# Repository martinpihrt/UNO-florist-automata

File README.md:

UNO florist automata Readme  
====

## UNO florist automata - Zavlažovač květin je založený na platformě Arduino a desce Arduino UNO<br>
(procesor ATMEGA328 a vlastní deska spojů)

Celý projekt je založen jako volný zdroj (lze použít pro nekomerční použití a přizpůsobit si k obrazu svému).<br>
K řídící desce je připojeno teplotní čidlo DS18B20, které měří teplotu půdy (pro možnost regulace zavlažování dle teploty)<br>
K řídící desce je také připojeno čidlo vlhkosti s frekvenčním výstupem 50Hz-5kHz (pro možnost regulace zavlažování dle vlhkosti) https://pihrt.com/elektronika/272-snimac-vlhkosti-pro-zalevaci-automat<br>
Veškeré nastavení automatu se provádí pomocí tlačítek a zobrazení údajů na 16x2 LCD displeji.<br>
Automat byl vyvinutý pro vertikální zavlažování rostlin, které má svá specifika zavlažování.<br>

## Pro více informací navštivte web...
Martin Pihrt - www.pihrt.com: https://pihrt.com/elektronika/400-uno-florist-automata<br>

## Pohled na desku a připojení čidel

## Video (fw 1.00 beta)

## Nastavení zavlažování dle dnů od pondělí do neděle

## Nastavení 3 nezávislých časů pro zavlažování s různou dobou provozu čerpadla

## Regulace dle vlhkosti
a) pokud je daný den a je čas programu 1 nebo je čas programu 2 nebo je čas programu 3 a vlhkost < 40% bude výsledná doba trvání závlahy + 1/2 trvání závlahy nastavené doby v menu. Tj. 150% času.<br>
b) pokud je daný den a je čas programu 1 nebo je čas programu 2 nebo je čas programu 3 a vlhkost >= 40% a < 60% bude výsledná doba trvání závlahy stejná jako nastavená doba v menu. Tj. 100% času.<br>
c) pokud je daný den a je čas programu 1 nebo je čas programu 2 a vlhkost >= 60% a < 80% bude výsledná doba trvání závlahy stejná jako nastavená doba v menu. Tj. 100% času.<br>
d) pokud je daný den a je čas programu 1 a vlhkost >= 60% bude výsledná doba trvání závlahy stejná jako nastavená doba v menu. Tj. 100% času.<br>
Z výše uvedeného vyplývá, že některé programy se s ohledem na vlhkost v určitém rozsahu vůbec nespustí, nebo bude výsledný čas upraven.<br>

<b>V žádném případě nepoužívejte obě regulace současně!</b>

## Regulece dle teploty
a) pokud je daný den a je čas programu 1 nebo je čas programu 2 nebo je čas programu 3 a teplota > 40°C bude výsledná doba trvání závlahy + 1/2 trvání závlahy nastavené doby v menu. Tj. 150% času.<br>
b) pokud je daný den a je čas programu 1 nebo je čas programu 2 nebo je čas programu 3 a teplota >= 30°C a < 40°C bude výsledná doba trvání závlahy stejná jako nastavená doba v menu. Tj. 100% času.<br>
c) pokud je daný den a je čas programu 1 nebo je čas programu 2 a teplota >= 20°C a < 30°C bude výsledná doba trvání závlahy stejná jako nastavená doba v menu. Tj. 100% času.<br>
d) pokud je daný den a je čas programu 1 a teplota >= 5°C a < 20°C bude výsledná doba trvání závlahy stejná jako nastavená doba v menu. Tj. 100% času.<br>
Z výše uvedeného vyplývá, že některé programy se s ohledem na teplotu v určitém rozsahu vůbec nespustí, nebo bude výsledný čas upraven.<br>

<b>V žádném případě nepoužívejte obě regulace současně!</b>

## Cyklování výstupu
V menu lze nastavit po jaké době běhu programu (1, 2, 3) se má výstup čerpadla vypnout a jako dobu má čekat vypnutý. Tato funkce umožňuje cyklování výstupu pro lepší vsakování vody do půdy (nedojde k přetékání květináče, ale k postupnému vsaku vody)<br>

Pokud nepožadujeme funkci cyklování nastavíme v menu "vypnout na dobu" na hodnotu 0s" a "vypnout čerpadlo po" na maximální hodnotu 250s.<br>
V grafu je vidět spínání výstupu (zap/vyp cyklování) s ohledem na vlhkost.<br>

## Nastavení datumu a času
Zleva nastavujeme den, měsíc, rok, hodina a minuta. Vteřina se při uložení nastaví na "0". Čas je ukládán do obvodu RTC DS1307.<br>

## Smazání do továrního nastavení
Pokud chceme zařízení vymazat do továrního nastavení stiskneme v menu jako níže na obrázku "ANO".<br>
<br>
* Výchozí údaje po resetu:<br>
* program 1 čas pro zavlažování 6:00<br>
* doba 30s<br>
* program 2 čas pro zavlažování 18:00<br>
* doba 30s<br>
* program 3 čas pro zavlažování 9:00<br> 
* doba 30s<br>
* vypnout čerpadlo po 5s<br>
* vypnout na dobu 20s<br>
* nepoužívat regulaci teplotou<br>
* nepoužívat regulaci vhlkostí<br>
* zavlažovat ve dnech po-ne<br>

## Uložit nastavení
Všechny parametry se ukládají do trvalé paměti EEPROM.<br>

## Připojení vstupů a výstupů  
* LCD:                    pin 8, 9,  2,  3,  6,  7 (Rs, E,DB4,DB5,DB6,DB7)<br>
* LCD podsvícení:         pin 10<br>
* Tlačítka IN:            pin 14 (A0 dělič 5 tlačítek)<br>
* Čidlo vlhka IN:         pin 5 (měří se frekvence ze snímače vlhkosti)<br>
* Serial:                 pin 0, 1<br>
* I2C:                    pin 18 (A4 SDA), 19 (A5 SCL) používá DS1307 adr. 0x68<br>
* Teplota:                pin 16  DS18B20 rudá +5V, černá GND, modrá (bílá) Data<br>
* Čerpadlo:               pin 17 (pro výstup - čerpadlo)<br>

## Verze FW, HW
* 1.00 výchozí verze desky a programu (měření vlhkosti pomocí frekvence)
* 1.10 upravená verze HW (přidán konektor na vstup A1) a FW (možnost měření vlhkosti pomocí sondy s napěťovým výstupem) příklad použité sondy: https://www.diymore.cc/products/2pcs-capacitive-soil-moisture-sensor-v1-2-analog-corrosion-resistant-dc-3-3-5-5v)
* 1.11 příprava na podporu více jazyků (zatím není hotové)

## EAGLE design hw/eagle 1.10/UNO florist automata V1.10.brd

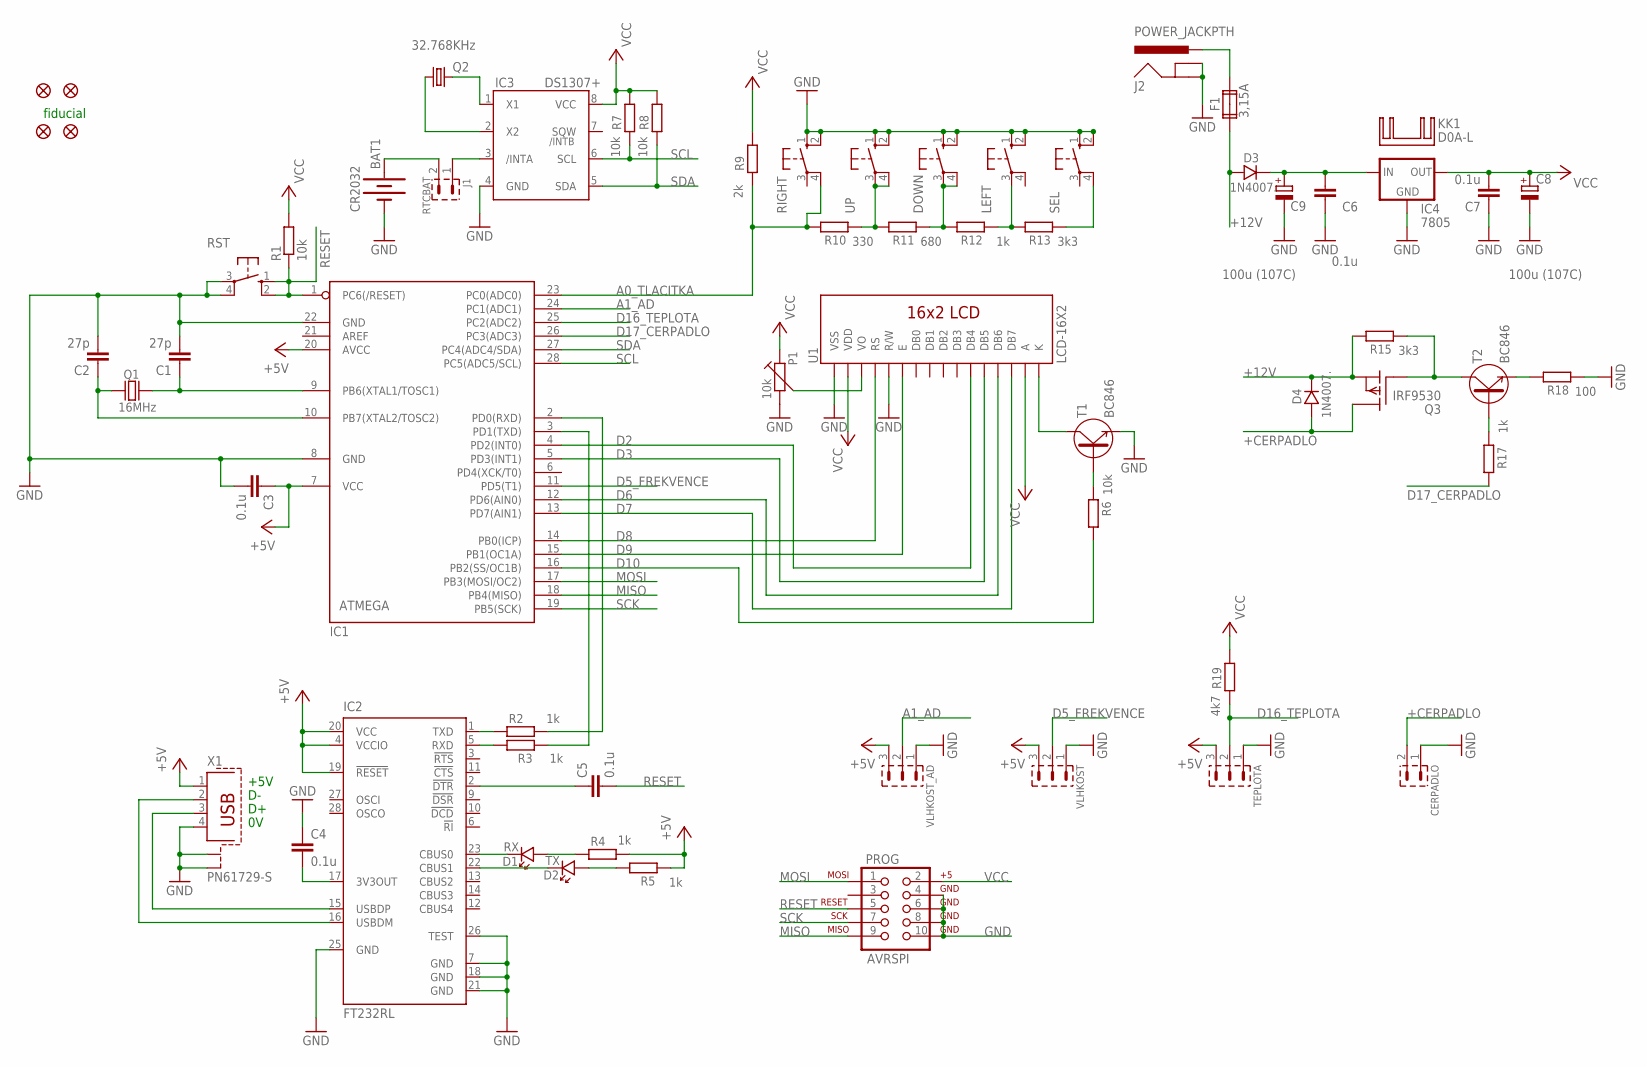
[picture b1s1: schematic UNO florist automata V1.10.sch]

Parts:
BAT1: CR2032; BATTCOM_20MM_PTH
C1, C2: 27p; C1206
C3, C4, C5, C6, C7: 0.1u; C1206
C8, C9: 100u (107C); C/6032-28W
CERPADLO: PSH02-02P
D1: RX; P1206
D2: TX; P1206
D3, D4: 1N4007.; SM-1
DOWN: 10-XX; B3F-10XX
F1: 3,15A; FUSE1
FID1, FID2, FID3, FID4: FIDUCIAL1.5X3; FIDUCIAL-1.5X3
IC1: ATMEGA; DIL28-3
IC2: FT232RL; SSOP28
IC3: DS1307+; SO08
IC4: 7805; 78XXL
J1: RTCBAT; S1G2_JUM
J2: POWER_JACKPTH; POWER_JACK_PTH
KK1: D0A-L; D02A-L
LEFT: 10-XX; B3F-10XX
P1: 10k; PT10V
PROG: AVRSPI; 2X5-SHROUDED_LOCK
Q1: 16MHz; HC-49U
Q2: 32.768KHz; TC38H
Q3: IRF9530; TO220
R1, R6, R7, R8: 10k; M1206
R2, R3, R4, R5, R12, R17: 1k; M1206
R9: 2k; M1206
R10: 330; M1206
R11: 680; M1206
R13, R15: 3k3; M1206
R18: 100; M1206
R19: 4k7; M1206
RIGHT: 10-XX; B3F-10XX
RST: 10-XX; B3F-10XX
SEL: 10-XX; B3F-10XX
T1, T2: BC846; SOT-23
TEPLOTA: PSH02-03P
U1: LCD-16X2; LCD-16X2_NOSILK
UP: 10-XX; B3F-10XX
VLHKOST: PSH02-03P
VLHKOST_AD: PSH02-03P
X1: PN61729-S

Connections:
+12V: D3.A, D4.K, F1.1A, Q3.3 (S), R15.2
+CERPADLO: CERPADLO.2, D4.A, Q3.2 (D)
A: IC3.2 (X2), Q2.1
A0_TLACITKA: IC1.23 (PC0(ADC0)), R9.1, R10.2, RIGHT.4 (P1)
A1_AD: IC1.24 (PC1(ADC1)), VLHKOST_AD.2
D2: IC1.4 (PD2(INT0)), U1.11 (DB4)
D3: IC1.5 (PD3(INT1)), U1.12 (DB5)
D5_FREKVENCE: IC1.11 (PD5(T1)), VLHKOST.2
D6: IC1.12 (PD6(AIN0)), U1.13 (DB6)
D7: IC1.13 (PD7(AIN1)), U1.14 (DB7)
D8: IC1.14 (PB0(ICP)), U1.4 (RS)
D9: IC1.15 (PB1(OC1A)), U1.6 (E)
D10: IC1.16 (PB2(SS/OC1B)), R6.2
D16_TEPLOTA: IC1.25 (PC2(ADC2)), R19.1, TEPLOTA.2
D17_CERPADLO: IC1.26 (PC3(ADC3)), R17.2
GND: BAT1.2 (-), C1.2, C2.2, C3.2, C4.1, C6.1, C7.1, C8.-, C9.-, CERPADLO.1, DOWN.1 (S), DOWN.2 (S1), IC1.8 (GND), IC1.22 (GND), IC2.7 (GND), IC2.18 (GND), IC2.21 (GND), IC2.25 (GND), IC2.26 (TEST), IC3.4 (GND), IC4.GND, J2.GND, J2.GNDBREAK, LEFT.1 (S), LEFT.2 (S1), P1.2, PROG.4, PROG.6, PROG.8, PROG.10, R18.1, RIGHT.1 (S), RIGHT.2 (S1), RST.3, RST.4 (P1), SEL.1 (S), SEL.2 (S1), T1.2 (E), TEPLOTA.1, U1.1 (VSS), U1.5 (R/W), UP.1 (S), UP.2 (S1), VLHKOST.1, VLHKOST_AD.1, X1.4, X1.S1, X1.S2
MISO: IC1.18 (PB4(MISO)), PROG.9
MOSI: IC1.17 (PB3(MOSI/OC2)), PROG.1
unnamed: IC2.16 (USBDM), X1.2
unnamed: IC2.15 (USBDP), X1.3
unnamed: C4.2, IC2.17 (3V3OUT)
unnamed: IC2.1 (TXD), R2.1
unnamed: IC2.5 (RXD), R3.2
unnamed: IC1.2 (PD0(RXD)), R2.2
unnamed: IC1.3 (PD1(TXD)), R3.1
unnamed: C5.1, IC2.2 (!DTR)
unnamed: D1.K, IC2.23 (CBUS0)
unnamed: D1.A, R4.1
unnamed: D2.K, IC2.22 (CBUS1)
unnamed: D2.A, R5.2
unnamed: BAT1.1 (+), J1.2
unnamed: IC3.3 (/INTA), J1.1
unnamed: T1.3 (C), U1.16 (K)
unnamed: R10.1, R11.2, UP.3, UP.4 (P1)
unnamed: DOWN.3, DOWN.4 (P1), R11.1, R12.2
unnamed: LEFT.3, R12.1, R13.2
unnamed: R13.1, SEL.4 (P1)
unnamed: F1.2A, J2.PWR
unnamed: C1.1, IC1.9 (PB6(XTAL1/TOSC1)), Q1.2
unnamed: C6.2, C9.+, D3.K, IC4.IN
unnamed: R6.1, T1.1 (B)
unnamed: C2.1, IC1.10 (PB7(XTAL2/TOSC2)), Q1.1
unnamed: Q3.1 (G), R15.1, T2.3 (C)
unnamed: R18.2, T2.2 (E)
unnamed: R17.1, T2.1 (B)
unnamed: P1.3, U1.3 (VO)
Q1: IC3.1 (X1), Q2.2
RESET: C5.2, IC1.1 (PC6(/RESET)), PROG.5, R1.1, RST.1 (S), RST.2 (S1)
SCK: IC1.19 (PB5(SCK)), PROG.7
SCL: IC1.28 (PC5(ADC5/SCL)), IC3.6 (SCL), R7.1
SDA: IC1.27 (PC4(ADC4/SDA)), IC3.5 (SDA), R8.1
VCC: C3.1, C7.2, C8.+, IC1.7 (VCC), IC1.20 (AVCC), IC2.4 (VCCIO), IC2.19 (!RESET), IC2.20 (VCC), IC3.8 (VCC), IC4.OUT, P1.1, PROG.2, R1.2, R4.2, R5.1, R7.2, R8.2, R9.2, R19.2, TEPLOTA.3, U1.2 (VDD), U1.15 (A), VLHKOST.3, VLHKOST_AD.3, X1.1

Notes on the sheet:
+5V
fiducial

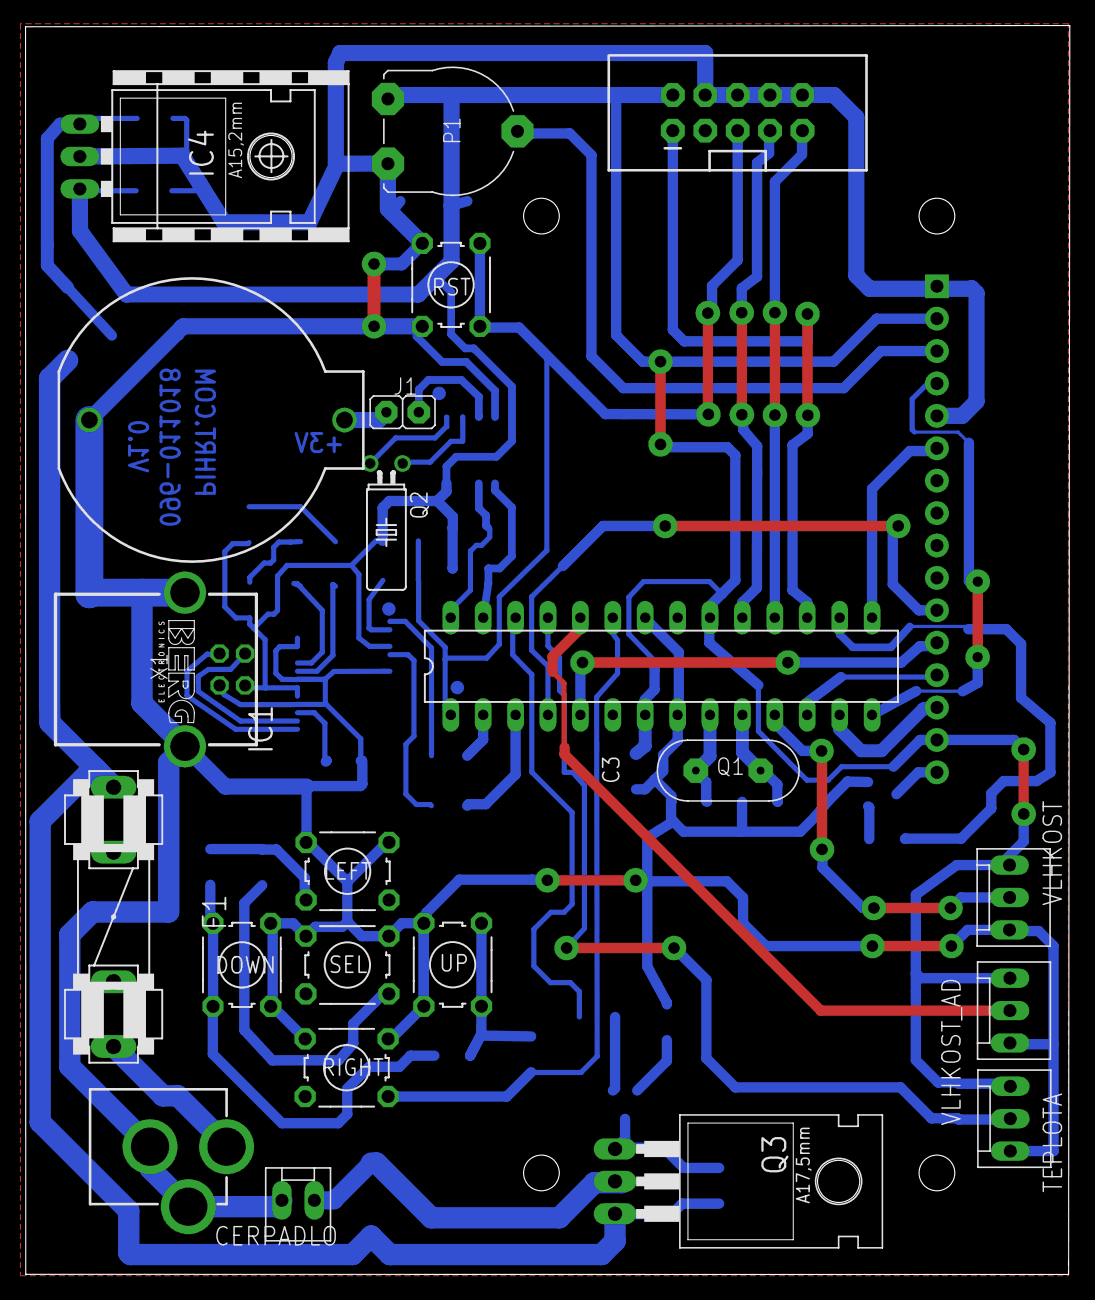
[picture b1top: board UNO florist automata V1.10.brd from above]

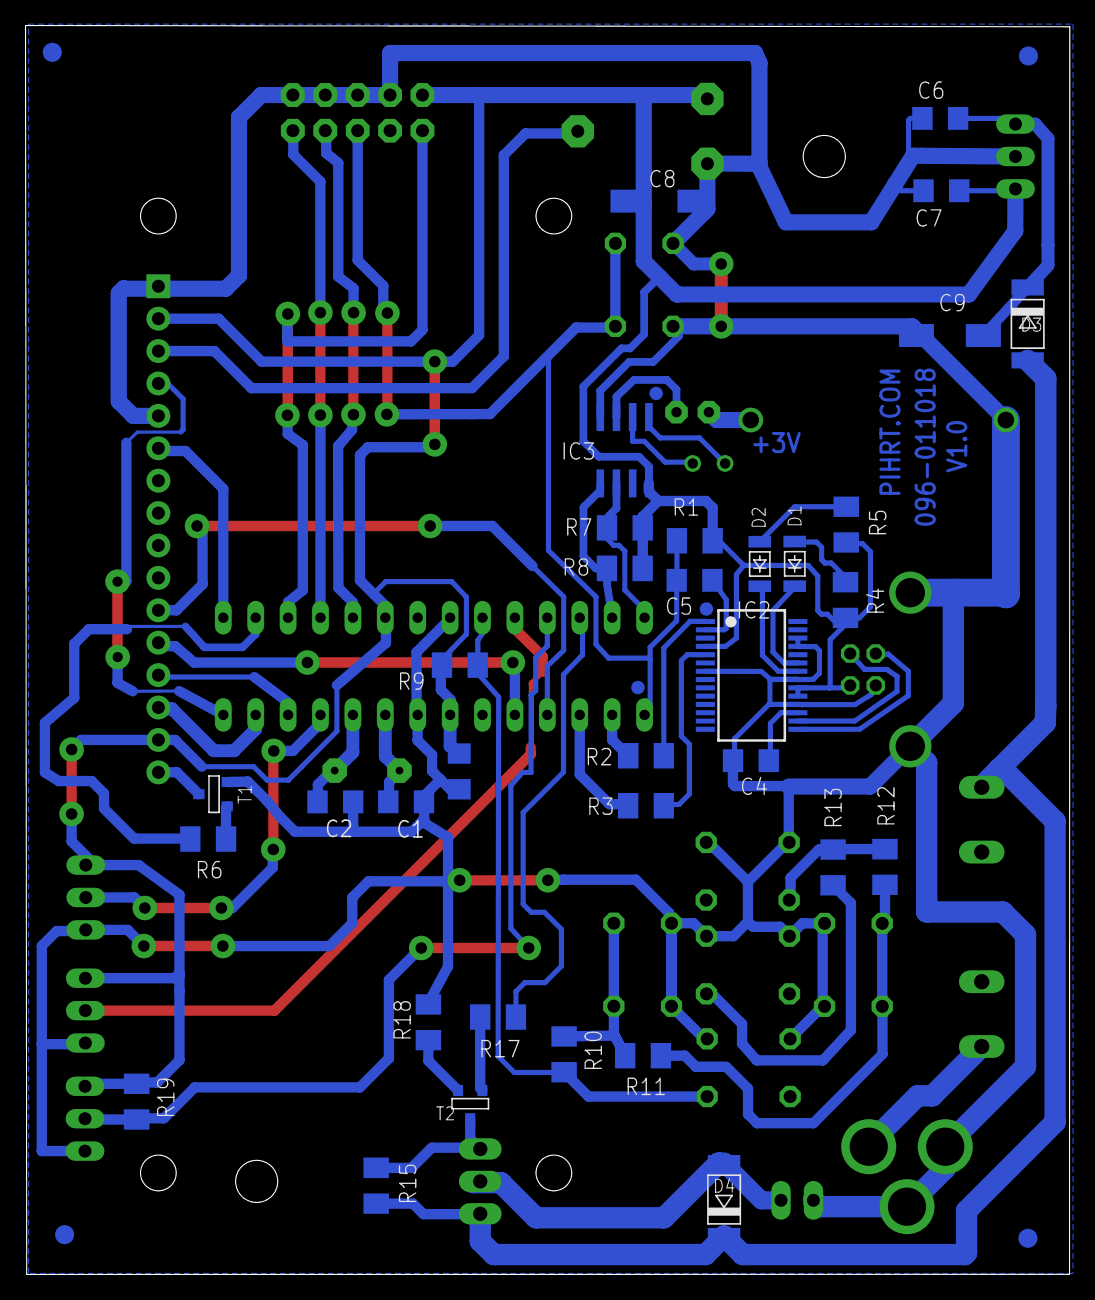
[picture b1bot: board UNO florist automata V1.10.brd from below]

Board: 2 copper layers, 81.9 x 97.9 mm, 62 parts (38 on the bottom side), 52 nets.

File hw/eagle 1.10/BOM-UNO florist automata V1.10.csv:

"Part";"Value";"Device";"Package";"Description";"MF";"MPN";"OC_FARNELL";"OC_NEWARK";"PROD_ID";
"BAT1";"CR2032";"BATTERY20PTH";"BATTCOM_20MM_PTH";"Battery Holders";"";"";"";"";"";
"C1";"27p";"C-EUC1206";"C1206";"CAPACITOR, European symbol";"";"";"";"";"";
"C2";"27p";"C-EUC1206";"C1206";"CAPACITOR, European symbol";"";"";"";"";"";
"C3";"0.1u";"C-EUC1206";"C1206";"CAPACITOR, European symbol";"";"";"";"";"";
"C4";"0.1u";"C-EUC1206";"C1206";"CAPACITOR, European symbol";"";"";"";"";"";
"C5";"0.1u";"C-EUC1206";"C1206";"CAPACITOR, European symbol";"";"";"";"";"";
"C6";"0.1u";"C-EUC1206";"C1206";"CAPACITOR, European symbol";"";"";"";"";"";
"C7";"0.1u";"C-EUC1206";"C1206";"CAPACITOR, European symbol";"";"";"";"";"";
"C8";"100u (107C)";"CPOL-EUC/6032-28W";"C/6032-28W";"POLARIZED CAPACITOR, European symbol";"";"";"";"";"";
"C9";"100u (107C)";"CPOL-EUC/6032-28W";"C/6032-28W";"POLARIZED CAPACITOR, European symbol";"";"";"";"";"";
"CERPADLO";"";"PSH02-02P";"PSH02-02P";"Konektory se zamkem - vidlice - 2pin";"";"";"";"";"";
"D1";"RX";"LED_1206";"P1206";"LED - jednobarevna";"";"";"";"";"";
"D2";"TX";"LED_1206";"P1206";"LED - jednobarevna";"";"";"";"";"";
"D3";"1N4007.";"1N4007.";"SM-1";"Usmernovaci dioda - 1A, 1000V";"";"";"";"";"";
"D4";"1N4007.";"1N4007.";"SM-1";"Usmernovaci dioda - 1A, 1000V";"";"";"";"";"";
"DOWN";"";"10-XX";"B3F-10XX";"OMRON SWITCH";"";"";"";"";"";
"F1";"3,15A";"FUSE2P";"FUSE1";"FUSE";"";"";"";"";"";
"FID1";"FIDUCIAL1.5X3";"FIDUCIAL1.5X3";"FIDUCIAL-1.5X3";"Fiducial Alignment Points";"";"";"";"";"";
"FID2";"FIDUCIAL1.5X3";"FIDUCIAL1.5X3";"FIDUCIAL-1.5X3";"Fiducial Alignment Points";"";"";"";"";"";
"FID3";"FIDUCIAL1.5X3";"FIDUCIAL1.5X3";"FIDUCIAL-1.5X3";"Fiducial Alignment Points";"";"";"";"";"";
"FID4";"FIDUCIAL1.5X3";"FIDUCIAL1.5X3";"FIDUCIAL-1.5X3";"Fiducial Alignment Points";"";"";"";"";"";
"IC1";"ATMEGA";"MEGA8-P";"DIL28-3";"MICROCONTROLLER";"";"";"";"";"";
"IC2";"FT232RL";"FT232RL";"SSOP28";"Source: http://www.ftdichip.com/Documents/DataSheets/DS_FT232R_v104.pdf";"";"FT232RL";"1146032";"91K9918";"";
"IC3";"DS1307+";"DS1337S+";"SO08";"RTC - obvod realneho casu";"";"";"";"";"";
"IC4";"7805";"78XXL";"78XXL";"VOLTAGE REGULATOR";"";"";"";"";"";
"J1";"RTCBAT";"S1G2_JUMP";"S1G2_JUM";"Radove konektory - koliky - 2x";"";"";"";"";"";
"J2";"POWER_JACKPTH";"POWER_JACKPTH";"POWER_JACK_PTH";"Power Jack";"";"";"";"";"PRT-00119";
"KK1";"D0A-L";"D0A-L";"D02A-L";"HEATSINK";"";"";"";"";"";
"LEFT";"";"10-XX";"B3F-10XX";"OMRON SWITCH";"";"";"";"";"";
"P1";"10k";"TRIMRPT10V";"PT10V";"Trimr";"";"";"";"";"";
"PROG";"AVRSPI";"AVR_SPI_PROG2LOCK";"2X5-SHROUDED_LOCK";"AVR 10-pin ICSP Header";"";"";"";"";"";
"Q1";"16MHz";"Q_HC-49U";"HC-49U";"Krystal";"";"";"";"";"";
"Q2";"32.768KHz";"CRYSTALTC38H";"TC38H";"CRYSTAL";"";"";"unknown";"unknown";"";
"Q3";"IRF9530";"IRF9530";"TO220";"P-Channel Enhancement MOSFET (HEXFET); -100V; -12A; 0,3Ohm";"";"";"";"";"";
"R1";"10k";"R-EU_M1206";"M1206";"RESISTOR, European symbol";"";"";"";"";"";
"R2";"1k";"R-EU_M1206";"M1206";"RESISTOR, European symbol";"";"";"";"";"";
"R3";"1k";"R-EU_M1206";"M1206";"RESISTOR, European symbol";"";"";"";"";"";
"R4";"1k";"R-EU_M1206";"M1206";"RESISTOR, European symbol";"";"";"";"";"";
"R5";"1k";"R-EU_M1206";"M1206";"RESISTOR, European symbol";"";"";"";"";"";
"R6";"10k";"R-EU_M1206";"M1206";"RESISTOR, European symbol";"";"";"";"";"";
"R7";"10k";"R-EU_M1206";"M1206";"RESISTOR, European symbol";"";"";"";"";"";
"R8";"10k";"R-EU_M1206";"M1206";"RESISTOR, European symbol";"";"";"";"";"";
"R9";"2k";"R-EU_M1206";"M1206";"RESISTOR, European symbol";"";"";"";"";"";
"R10";"330";"R-EU_M1206";"M1206";"RESISTOR, European symbol";"";"";"";"";"";
"R11";"680";"R-EU_M1206";"M1206";"RESISTOR, European symbol";"";"";"";"";"";
"R12";"1k";"R-EU_M1206";"M1206";"RESISTOR, European symbol";"";"";"";"";"";
"R13";"3k3";"R-EU_M1206";"M1206";"RESISTOR, European symbol";"";"";"";"";"";
"R15";"3k3";"R-EU_M1206";"M1206";"RESISTOR, European symbol";"";"";"";"";"";
"R17";"1k";"R-EU_M1206";"M1206";"RESISTOR, European symbol";"";"";"";"";"";
"R18";"100";"R-EU_M1206";"M1206";"RESISTOR, European symbol";"";"";"";"";"";
"R19";"4k7";"R-EU_M1206";"M1206";"RESISTOR, European symbol";"";"";"";"";"";
"RIGHT";"";"10-XX";"B3F-10XX";"OMRON SWITCH";"";"";"";"";"";
"RST";"";"10-XX";"B3F-10XX";"OMRON SWITCH";"";"";"";"";"";
"SEL";"";"10-XX";"B3F-10XX";"OMRON SWITCH";"";"";"";"";"";
"T1";"BC846";"BC846";"SOT-23";"SMD tranzistor - NPN - ekv. BC546";"";"";"";"";"";
"T2";"BC846";"BC846";"SOT-23";"SMD tranzistor - NPN - ekv. BC546";"";"";"";"";"";
"TEPLOTA";"";"PSH02-03P";"PSH02-03P";"Konektory se zamkem - vidlice - 3pin";"";"";"";"";"";
"U1";"LCD-16X2";"LCD-16X2NOSILK";"LCD-16X2_NOSILK";"Standard text-only 16x2 parallel input LCD";"";"";"";"";"";
"UP";"";"10-XX";"B3F-10XX";"OMRON SWITCH";"";"";"";"";"";
"VLHKOST";"";"PSH02-03P";"PSH02-03P";"Konektory se zamkem - vidlice - 3pin";"";"";"";"";"";
"VLHKOST_AD";"";"PSH02-03P";"PSH02-03P";"Konektory se zamkem - vidlice - 3pin";"";"";"";"";"";
"X1";"PN61729-S";"PN61729-S";"PN61729-S";"BERG USB connector";"";"";"unknown";"unknown";"";

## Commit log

2018-10-01 Create project
2018-10-05 Not ready - prepare
2018-10-05 First test
2018-10-13 beta
2018-10-13 Fix bug
2018-10-14 LCD foto
2018-10-14 Add a fix
2018-10-16 prepare
2018-10-17 přeformátování
2018-10-17 vypisování tlacitek do serialu
2018-10-17 predelani ==false na !
2018-10-17 predelani promennych
2018-10-19 Testovací verze RC1
    oprava chyb, přidaná funkce výpisu na LCD uběhlého času právě spuštěného programu. Potom s zobrazuje například: čerpadlo ZAP 5/25 sec
2019-02-21 Add new FW1.10
    not tested - beta
2019-02-22 ok try it :-)
2019-02-22 Přidaná verze HW a FW 1.10
2019-03-01 graf
2019-03-01 Prepare language

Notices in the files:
parts and their libraries:
Copyright (C) PaJa 2001-2014
SparkFun-Electromechanical: Licensing: Creative Commons ShareAlike 4.0 International - https://creativecommons.org/licenses/by-sa/4.0
Copyright (C) PaJa 2011-2014
